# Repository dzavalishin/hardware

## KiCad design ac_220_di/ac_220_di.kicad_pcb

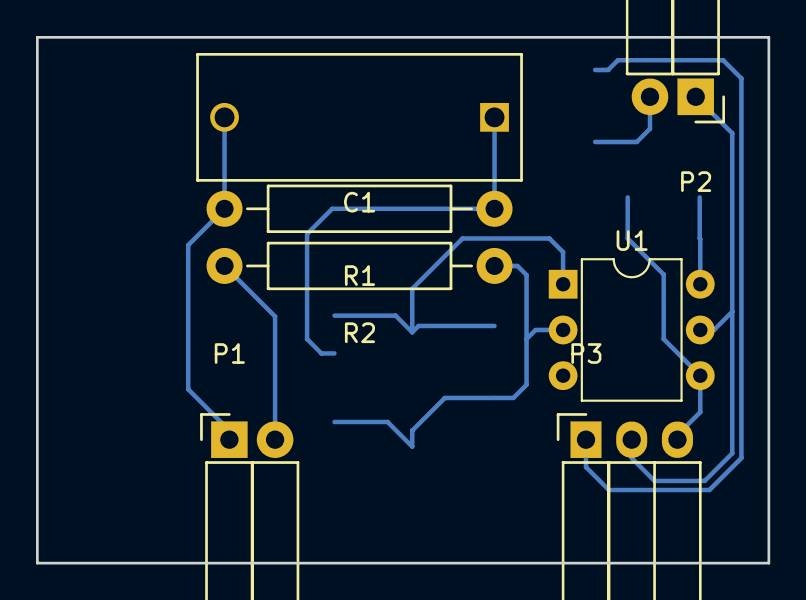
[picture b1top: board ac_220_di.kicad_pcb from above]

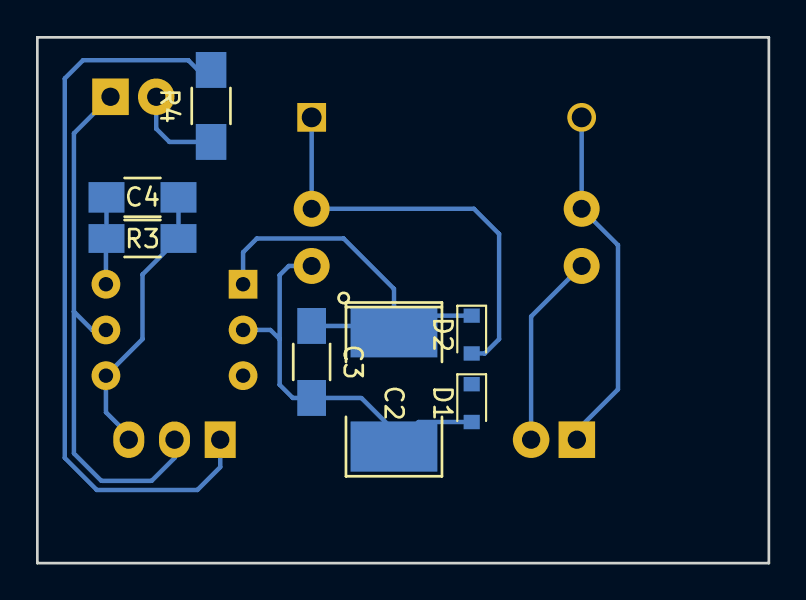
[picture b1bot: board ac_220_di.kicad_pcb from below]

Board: 2 copper layers, 40.6 x 29.2 mm, 14 parts (7 on the bottom side), 10 nets.

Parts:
C1: 0.15uF; C_Rect_L18_W7_P15
C2: 10,0; SMD-2112_Pol
C3: 0,1; C_1206_HandSoldering
C4: 100pf; C_1206_HandSoldering
D1, D2: 4448; D_0805
P1: In; Socket_Strip_Angled_1x02
P2: Led; Socket_Strip_Angled_1x02
P3: Out; Socket_Strip_Angled_1x03
R1: 3m; Resistor_Horizontal_RM15mm
R2: 10k 1W; Resistor_Horizontal_RM15mm
R3: 470k; R_1206_HandSoldering
R4: 4,7k (10ma) or 12k (2ma); R_1206_HandSoldering
U1: 4N35; DIP-6_W7.62mm

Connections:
unnamed: C1.1, D1.1, D2.2, R1.1
unnamed: C1.2, P1.1, R1.2
unnamed: C2.1, C3.1, D2.1, U1.1
unnamed: C2.2, C3.2, D1.2, R2.1, U1.2
unnamed: C4.1, R3.2, U1.6
unnamed: C4.2, P3.3, R3.1, U1.4
unnamed: P1.2, R2.2
unnamed: P2.1, P3.2, U1.5
unnamed: P2.2, R4.1
unnamed: P3.1, R4.2

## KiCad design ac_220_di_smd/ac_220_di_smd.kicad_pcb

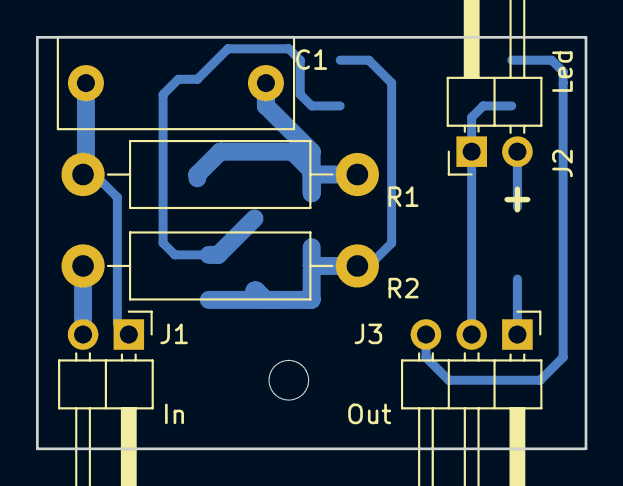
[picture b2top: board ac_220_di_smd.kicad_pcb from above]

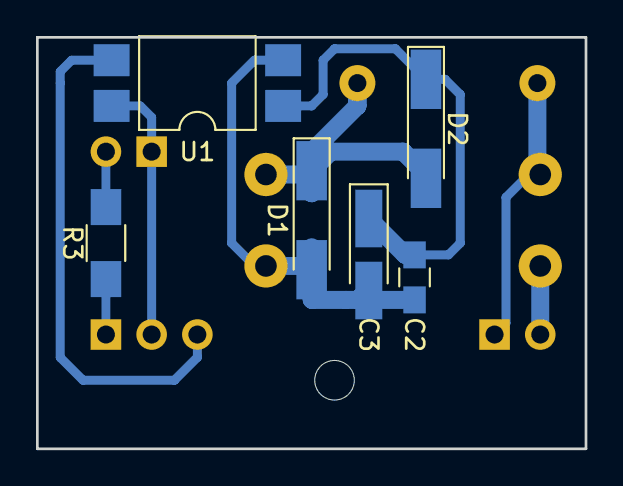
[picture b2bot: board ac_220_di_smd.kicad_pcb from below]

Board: 2 copper layers, 30.5 x 22.9 mm, 12 parts (6 on the bottom side), 9 nets.

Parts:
C1: 0,15uF 400v; C_Rect_L13.0mm_W5.0mm_P10.00mm_FKS3_FKP3_MKS4
C2: 0,1; C_0805_HandSoldering
C3: 10,0; CP_Tantalum_Case-A_EIA-3216-18_Hand
D1, D2: 4448; D_MiniMELF_Handsoldering
J1: In; Pin_Header_Angled_1x02_Pitch2.54mm
J2: Led; Pin_Header_Angled_1x02_Pitch2.54mm
J3: Out; Pin_Header_Angled_1x03_Pitch2.54mm
R1: 3m; R_Axial_DIN0411_L9.9mm_D3.6mm_P15.24mm_Horizontal
R2: 10k 1W; R_Axial_DIN0411_L9.9mm_D3.6mm_P15.24mm_Horizontal
R3: 4,7k; R_1206_HandSoldering
U1: PC817; SMDIP-4_W9.53mm

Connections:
unnamed: C1.1, D1.1, D2.2, R1.1
unnamed: C1.2, J1.1, R1.2
unnamed: C2.1, C3.2, D1.2, R2.1, U1.2
unnamed: C2.2, C3.1, D2.1, U1.1
unnamed: J1.2, R2.2
unnamed: J2.1, J3.2, U1.4
unnamed: J2.2, R3.2
unnamed: J3.1, R3.1
unnamed: J3.3, U1.3

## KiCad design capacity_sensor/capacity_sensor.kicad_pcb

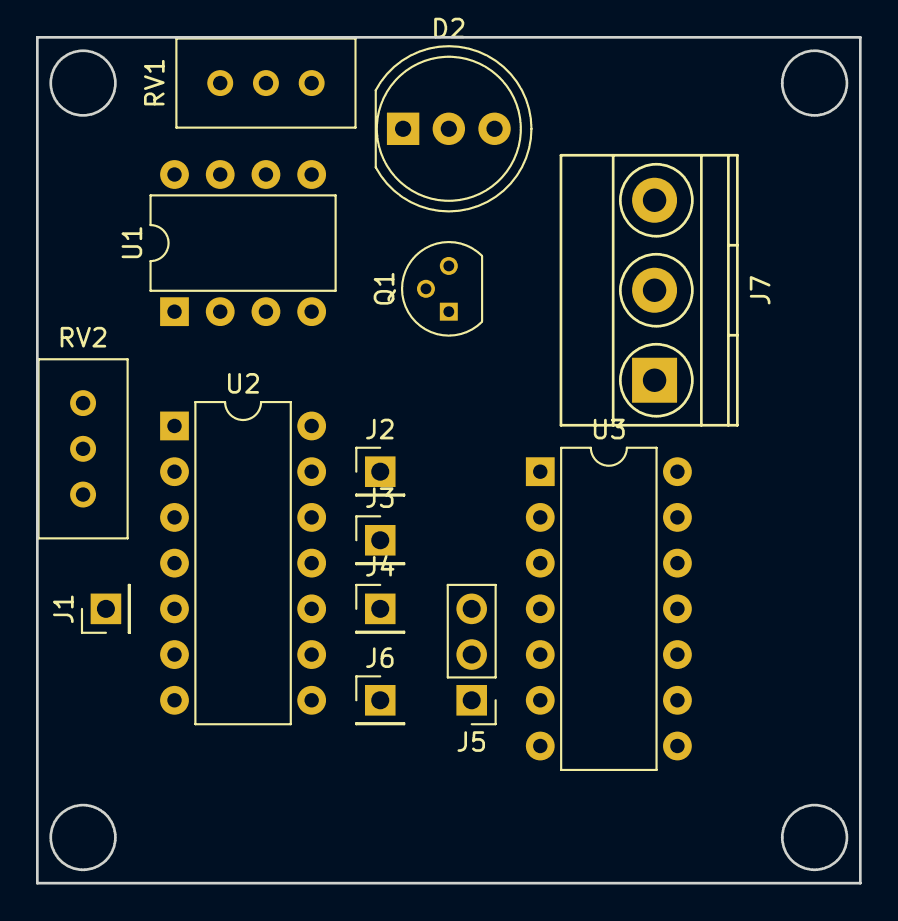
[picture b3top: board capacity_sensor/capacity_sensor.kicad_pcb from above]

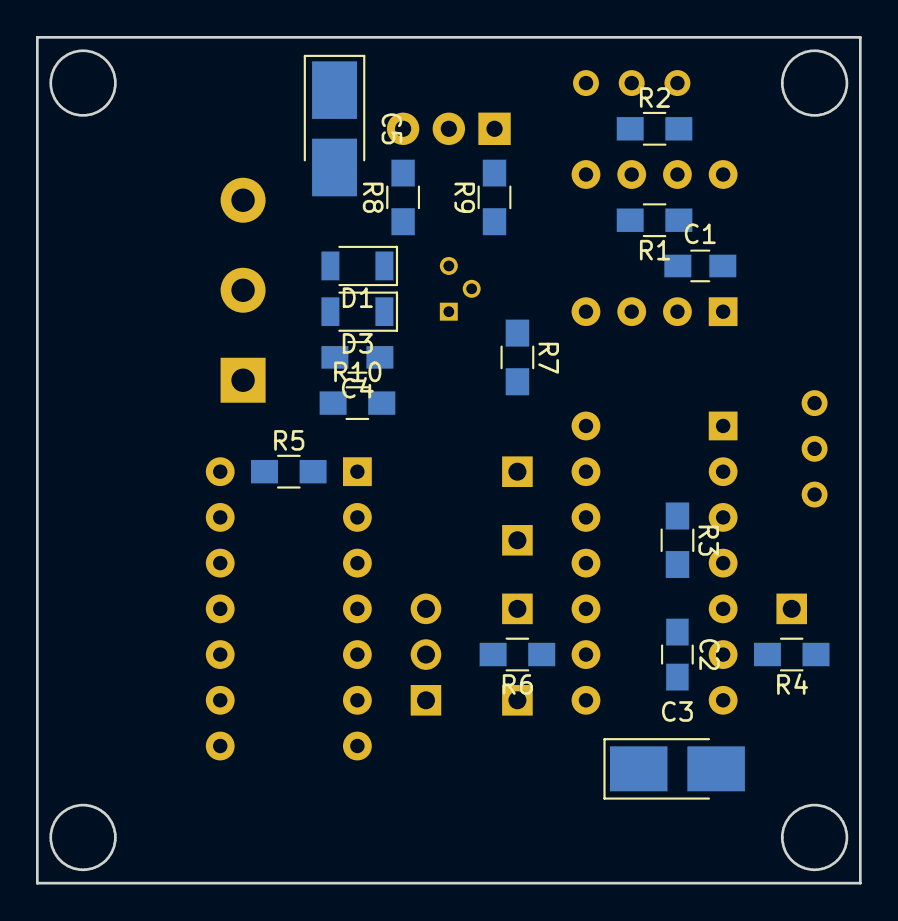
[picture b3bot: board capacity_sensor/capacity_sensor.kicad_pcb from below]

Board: 2 copper layers, 45.7 x 47.0 mm, 31 parts (17 on the bottom side), 28 nets, no tracks yet.

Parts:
C1: 2n2; C_0805_HandSoldering
C2: 10pF; C_0805_HandSoldering
C3, C5: 10,0; CP_Tantalum_Case-B_EIA-3528-21_Hand
C4: 0,1; C_0805_HandSoldering
D1, D3: 1N4148; D_1206
D2: LED_Dual_CAC; LED_D8.0mm-3
J1: TP1; Pin_Header_Straight_1x01_Pitch2.54mm
J2: Sensor; Pin_Header_Straight_1x01_Pitch2.54mm
J3: TP2; Pin_Header_Straight_1x01_Pitch2.54mm
J4: TP3; Pin_Header_Straight_1x01_Pitch2.54mm
J5: Polarity; Pin_Header_Straight_1x03_Pitch2.54mm
J6: TP4; Pin_Header_Straight_1x01_Pitch2.54mm
J7: Pwr/Out; TerminalBlock_Phoenix_MKDS1.5-3pol
Q1: BC546; TO-92_Molded_Narrow
R1, R2, R5, R7, R8: 1k; R_0805_HandSoldering
R3, R6: 10k; R_0805_HandSoldering
R4: 2k; R_0805_HandSoldering
R9: 5k6; R_0805_HandSoldering
R10: 100; R_0805_HandSoldering
RV1: 10k; Potentiometer_Trimmer_Suntan_TSR-3386C_Vertical
RV2: 50k; Potentiometer_Trimmer_Suntan_TSR-3386C_Vertical
U1: ICM7555; DIP-8_W7.62mm
U2: 74HCT14; DIP-14_W7.62mm
U3: 74HC74; DIP-14_W7.62mm

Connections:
+5V: C5.1, D2.2, J7.1, R5.1, RV1.1, RV1.2, U1.8, U2.14, U3.14
GND: C1.2, C2.2, C3.2, C4.2, C5.2, J7.3, Q1.3, R9.1, U1.1, U2.7, U3.7
unnamed: C1.1, R1.2, U1.2, U1.6
unnamed: C2.1, RV2.1, RV2.2, U2.11
unnamed: C3.1, R6.1, U2.9
unnamed: C4.1, D3.2, R10.2
unnamed: D1.1, D3.1, Q1.1
unnamed: D1.2, R8.1
unnamed: D2.1, R9.2
unnamed: D2.3, R8.2
unnamed: J1.1, U2.2, U2.3, U2.5
unnamed: J2.1, R3.1, U2.13
unnamed: J3.1, U2.12, U3.2
unnamed: J4.1, U2.10, U3.3
unnamed: J5.1, U3.6
unnamed: J5.2, R6.2
unnamed: J5.3, U3.5, U3.11
unnamed: J6.1, R7.2, U2.8
unnamed: J7.2, R10.1
unnamed: Q1.2, R7.1
unnamed: R1.1, R2.2, U1.7
unnamed: R2.1, RV1.3
unnamed: R3.2, U2.4
unnamed: R4.1, RV2.3
unnamed: R4.2, U2.6
unnamed: R5.2, U3.1, U3.4, U3.10, U3.13
unnamed: U1.3, U2.1
unnamed: U3.8, U3.12

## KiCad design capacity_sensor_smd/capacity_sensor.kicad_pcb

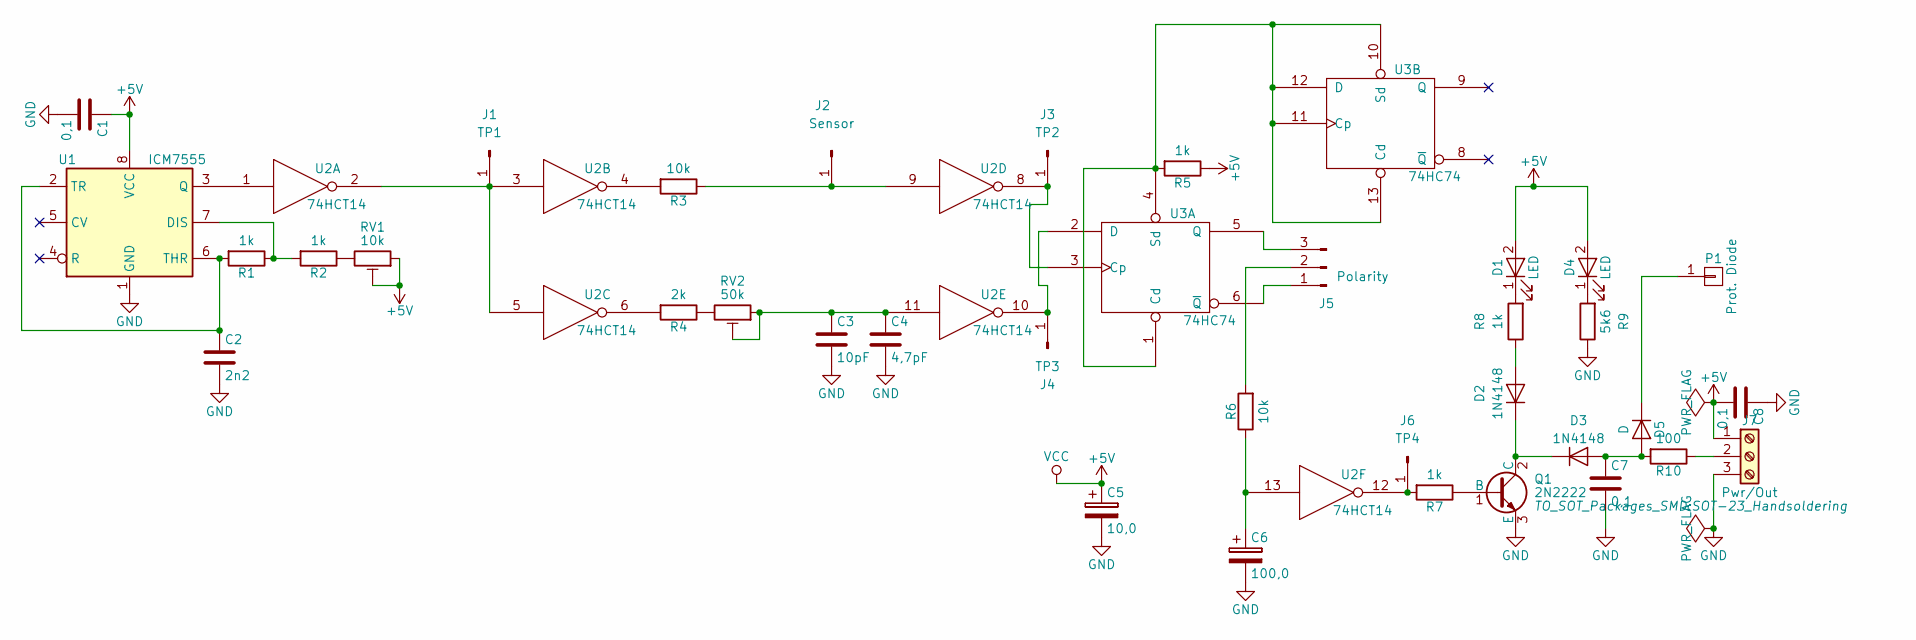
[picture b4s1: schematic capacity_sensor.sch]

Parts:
C1, C7, C8: 0,1; C_0805_HandSoldering
C2: 2n2; C_0805_HandSoldering
C3: 10pF; C_0805_HandSoldering
C4: 4,7pF; C_0805_HandSoldering
C5: 10,0; CP_Tantalum_Case-A_EIA-3216-18_Hand
C6: 100,0; CP_Tantalum_Case-B_EIA-3528-21_Hand
D1, D4: LED; LED_1206_HandSoldering
D2, D3: 1N4148; D_1206
D5: D; D_PowerDI-123
J1: TP1; Pin_Header_Straight_1x01_Pitch2.54mm
J2: Sensor; Pin_Header_Straight_1x01_Pitch2.54mm
J3: TP2; Pin_Header_Straight_1x01_Pitch2.54mm
J4: TP3; Pin_Header_Straight_1x01_Pitch2.54mm
J5: Polarity; Pin_Header_Straight_1x03_Pitch2.54mm
J6: TP4; Pin_Header_Straight_1x01_Pitch2.54mm
J7: Pwr/Out; TerminalBlock_Altech_AK300-3_P5.00mm
P1: Prot. Diode; Pin_Header_Straight_1x01_Pitch2.54mm
Q1: 2N2222; SOT-23_Handsoldering
R1, R2, R5, R7, R8: 1k; R_0805_HandSoldering
R3, R6: 10k; R_0805_HandSoldering
R4: 2k; R_0805_HandSoldering
R9: 5k6; R_0805_HandSoldering
R10: 100; R_0805_HandSoldering
RV1: 10k; Potentiometer_Trimmer_Suntan_TSR-3386C_Vertical
RV2: 50k; Potentiometer_Trimmer_Suntan_TSR-3386C_Vertical
U1: ICM7555; DIP-8_W7.62mm
U2: 74HCT14; SOIC-14_3.9x8.7mm_Pitch1.27mm
U3: 74HC74; SOIC-14_3.9x8.7mm_Pitch1.27mm

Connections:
+5V: C1.1, C5.1, C8.2, D1.2 (A), D4.2 (A), J7.1, R5.1, RV1.1, RV1.2, U1.8 (VCC), U2.14 (VCC), U3.14 (VCC)
GND: C1.2, C2.2, C3.2, C4.2, C5.2, C6.2, C7.2, C8.1, J7.3, Q1.3 (E), R9.1, U1.1 (GND), U2.7 (GND), U3.7 (GND)
unnamed: C2.1, R1.2, U1.2 (TR), U1.6 (THR)
unnamed: C3.1, C4.1, RV2.1, RV2.2, U2.11
unnamed: C6.1, R6.1, U2.13
unnamed: C7.1, D3.2 (A), D5.2 (A), R10.2
unnamed: D1.1 (K), R8.2
unnamed: D2.1 (K), D3.1 (K), Q1.2 (C)
unnamed: D2.2 (A), R8.1
unnamed: D4.1 (K), R9.2
unnamed: D5.1 (K), P1.1
unnamed: J1.1, U2.2, U2.3, U2.5
unnamed: J2.1, R3.1, U2.9
unnamed: J3.1, U2.8, U3.3 (Cp)
unnamed: J4.1, U2.10, U3.2 (D)
unnamed: J5.1, U3.6 (~Q)
unnamed: J5.2, R6.2
unnamed: J5.3, U3.5 (Q)
unnamed: J6.1, R7.2, U2.12
unnamed: J7.2, R10.1
unnamed: Q1.1 (B), R7.1
unnamed: R1.1, R2.2, U1.7 (DIS)
unnamed: R2.1, RV1.3
unnamed: R3.2, U2.4
unnamed: R4.1, RV2.3
unnamed: R4.2, U2.6
unnamed: R5.2, U3.1 (Cd), U3.4 (Sd), U3.10 (Sd), U3.11 (Cp), U3.12 (D), U3.13 (Cd)
unnamed: U1.3 (Q), U2.1

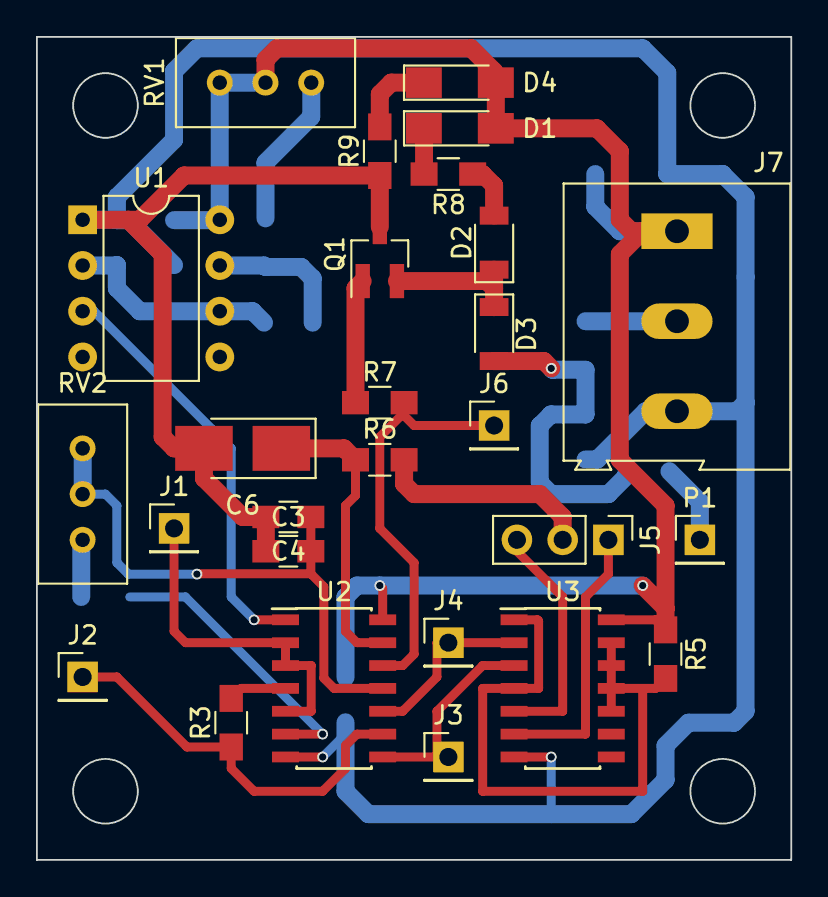
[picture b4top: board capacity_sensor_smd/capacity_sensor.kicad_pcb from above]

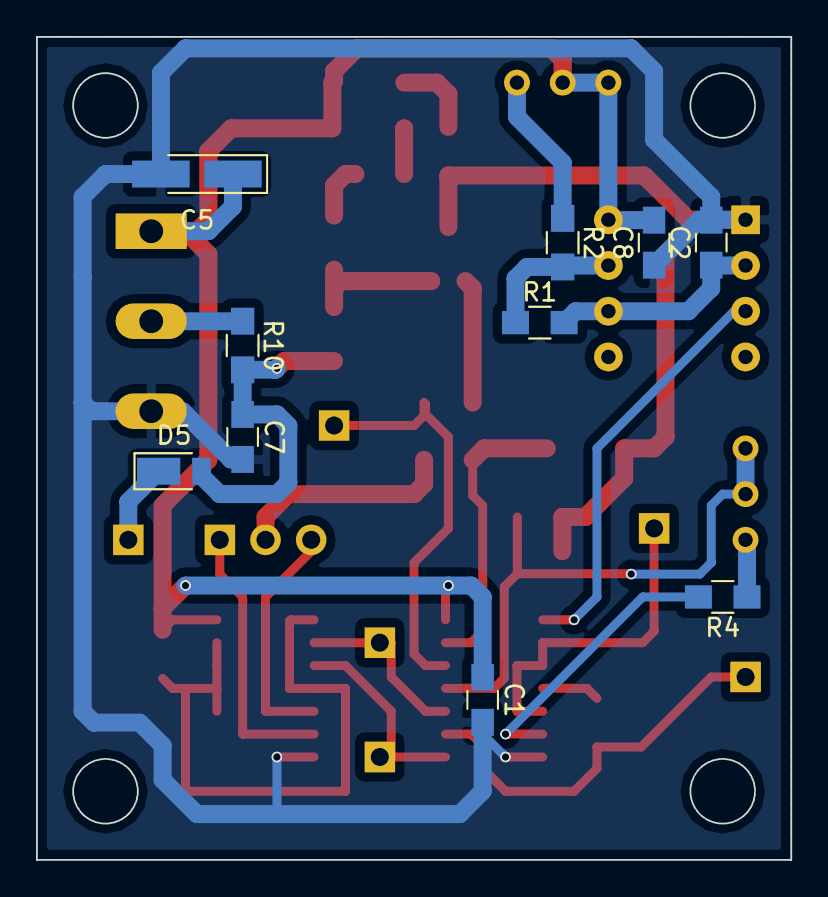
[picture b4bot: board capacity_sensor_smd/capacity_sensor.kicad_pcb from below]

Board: 2 copper layers, 41.9 x 45.7 mm, 37 parts (10 on the bottom side), 28 nets.

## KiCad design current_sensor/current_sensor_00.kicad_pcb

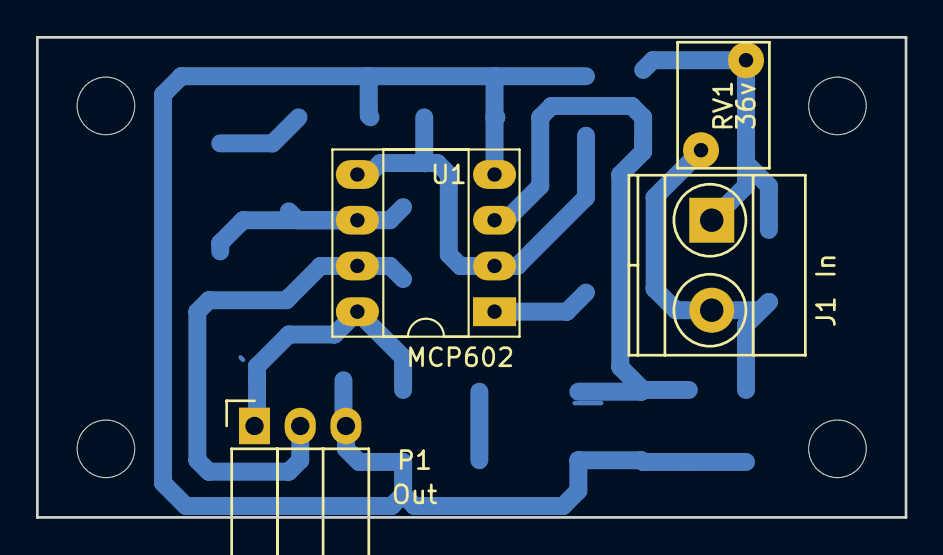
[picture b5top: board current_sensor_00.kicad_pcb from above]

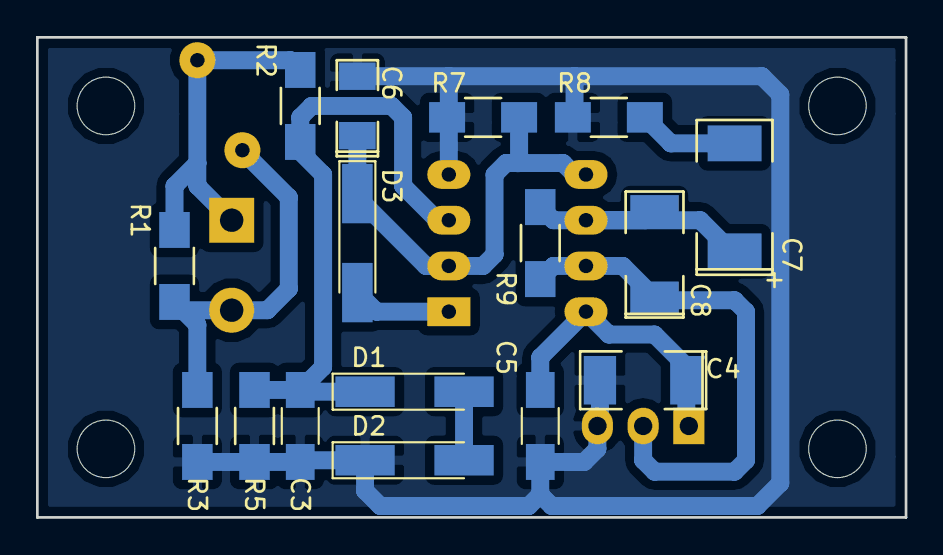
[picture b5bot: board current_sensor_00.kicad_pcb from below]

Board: 2 copper layers, 48.3 x 26.7 mm, 20 parts (16 on the bottom side), 11 nets.

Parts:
C3: 15nF; C_1206_HandSoldering
C4, C8: 10,0; SMD-2010_Pol
C5: 0,1; C_1206_HandSoldering
C6: 1,0; SMD-1206_Pol
C7: 100,0; SMD-2512_Pol
D1, D2: 3v9; D_MiniMELF_Handsoldering
D3: 1N4148; D_MiniMELF_Handsoldering
J1: In; TerminalBlock_Pheonix_MKDS1.5-2pol
P1: Out; Socket_Strip_Angled_1x03
R1: 100; R_1206_HandSoldering
R2, R3: 1k; R_1206_HandSoldering
R5, R9: 1M; R_1206_HandSoldering
R7: 510k; R_1206_HandSoldering
R8: 100k; R_1206_HandSoldering
RV1: 36v; RV_Disc_D7_W5.1_P5
U1: MCP602; DIP-8_W7.62mm_Socket_LongPads

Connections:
+5V: C4.1, C5.1, P1.1, U1.8
/InA: J1.1, R1.1, R2.1, RV1.1
/InB: J1.2, R1.2, R3.2, RV1.2
/Out: C8.1, P1.2, R9.1, U1.7
GND: C3.2, C4.2, C5.2, C6.2, D2.1, P1.3, R3.1, R5.2, R7.2, R8.2, U1.4
unnamed: C3.1, D1.1, R2.2, R5.1, U1.3
unnamed: C6.1, D3.1, R7.1, U1.2, U1.5
unnamed: C7.1, C8.2, R9.2, U1.6
unnamed: C7.2, R8.1
unnamed: D1.2, D2.2
unnamed: D3.2, U1.1
